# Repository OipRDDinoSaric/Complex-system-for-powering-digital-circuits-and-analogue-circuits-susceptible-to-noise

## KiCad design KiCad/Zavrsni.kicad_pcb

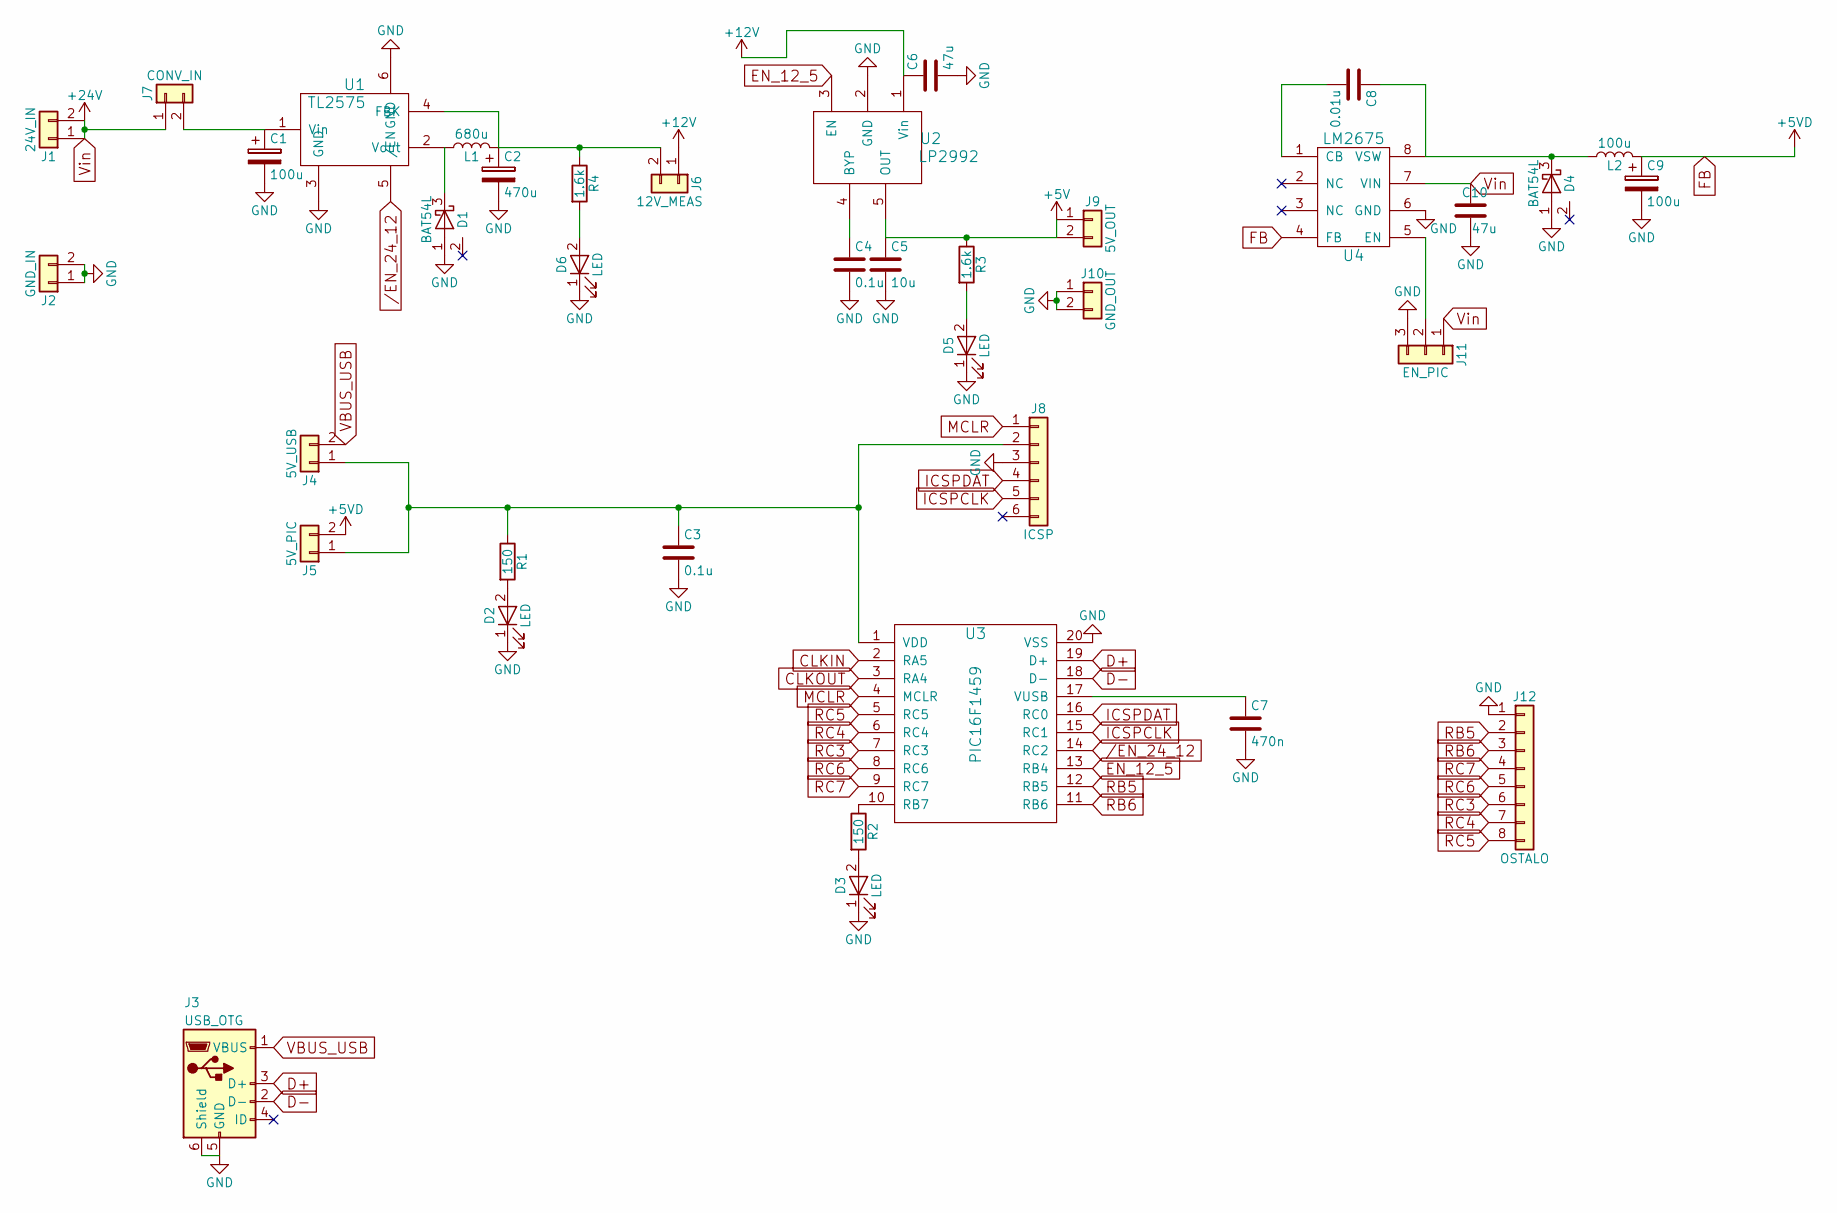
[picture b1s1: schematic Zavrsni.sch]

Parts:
C1: 100u; CP_Elec_6.3x7.7
C2: 470u; CP_Elec_10x10.5
C3: 0.1u; C_0402
C4: 0.1u; C_0805_HandSoldering
C5: 10u; C_1210_HandSoldering
C6, C10: 47u; C_1210_HandSoldering
C7: 470n; C_0805_HandSoldering
C8: 0.01u; C_0603_HandSoldering
C9: 100u; SM2917_POL
D1, D4: BAT54L; SOT-23_Handsoldering
D2, D3: LED; C_0603_HandSoldering
D5, D6: LED; Zelena dioda
J1: 24V_IN; Pin_Header_Straight_1x02_Pitch2.54mm
J2: GND_IN; Pin_Header_Straight_1x02_Pitch2.54mm
J3: USB_OTG; USB_Micro-B
J4: 5V_USB; Pin_Header_Straight_1x02_Pitch2.54mm
J5: 5V_PIC; Pin_Header_Straight_1x02_Pitch2.54mm
J6: 12V_MEAS; Pin_Header_Straight_1x02_Pitch2.54mm
J7: CONV_IN; Pin_Header_Straight_1x02_Pitch2.54mm
J8: ICSP; Pin_Header_Straight_1x06_Pitch2.54mm
J9: 5V_OUT; Pin_Header_Straight_1x02_Pitch2.54mm
J10: GND_OUT; Pin_Header_Straight_1x02_Pitch2.54mm
J11: EN_PIC; Pin_Header_Straight_1x03_Pitch2.54mm
J12: OSTALO; Pin_Header_Straight_1x08_Pitch2.54mm
L1: 680u; Coilcraft MSS1278T-684KLB 680uH
L2: 100u; Bourns_SRF0703A-101M_100u
R1, R2: 150; R_0805_HandSoldering
R3, R4: 1.6k; R_0402
U1: TL2575; TO-263-5
U2: LP2992; SOT-23-5_HandSoldering
U3: PIC16F1459; DIP-20_W7.62mm_LongPads
U4: LM2675; SOIC-8_3.9x4.9mm_Pitch1.27mm

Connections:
+5V: C5.1, J9.1, J9.2, R3.1, U2.5 (OUT)
+12V: C6.1, J6.1, U2.1 (Vin)
/EN_24_12: U1.5 (/EN), U3.14 (RC2)
CLKIN: U3.2 (RA5)
CLKOUT: U3.3 (RA4)
D+: J3.3 (D+), U3.19 (D+)
D-: J3.2 (D-), U3.18 (D-)
EN_12_5: U2.3 (EN), U3.13 (RB4)
FB: C9.1, J5.2, L2.2, U4.4 (FB)
GND: C1.2, C2.2, C3.2, C4.2, C5.2, C6.2, C7.2, C9.2, C10.1, D1.1 (A), D2.1 (K), D3.1 (K), D4.1 (A), D5.1 (K), D6.1 (K), J2.1, J2.2, J3.5 (GND), J3.6 (Shield), J8.3, J10.1, J10.2, J11.3, J12.1, U1.3 (GND), U1.6 (GND), U2.2 (GND), U3.20 (VSS), U4.6 (GND)
ICSPCLK: J8.5, U3.15 (RC1)
ICSPDAT: J8.4, U3.16 (RC0)
MCLR: J8.1, U3.4 (MCLR)
unnamed: C1.1, J7.2, U1.1 (Vin)
unnamed: C2.1, J6.2, L1.2, R4.1, U1.4 (FBK)
unnamed: C3.1, J4.1, J5.1, J8.2, R1.1, U3.1 (VDD)
unnamed: C4.1, U2.4 (BYP)
unnamed: C7.1, U3.17 (VUSB)
unnamed: C8.1, D4.3 (K), L2.1, U4.8 (VSW)
unnamed: C8.2, U4.1 (CB)
unnamed: D1.3 (K), L1.1, U1.2 (Vout)
unnamed: D2.2 (A), R1.2
unnamed: D3.2 (A), R2.2
unnamed: D5.2 (A), R3.2
unnamed: D6.2 (A), R4.2
unnamed: J11.2, U4.5 (EN)
unnamed: R2.1, U3.10 (RB7)
RB5: J12.2, U3.12 (RB5)
RB6: J12.3, U3.11 (RB6)
RC3: J12.6, U3.7 (RC3)
RC4: J12.7, U3.6 (RC4)
RC5: J12.8, U3.5 (RC5)
RC6: J12.5, U3.8 (RC6)
RC7: J12.4, U3.9 (RC7)
VBUS_USB: J3.1 (VBUS), J4.2
Vin: C10.2, J1.1, J1.2, J7.1, J11.1, U4.7 (VIN)

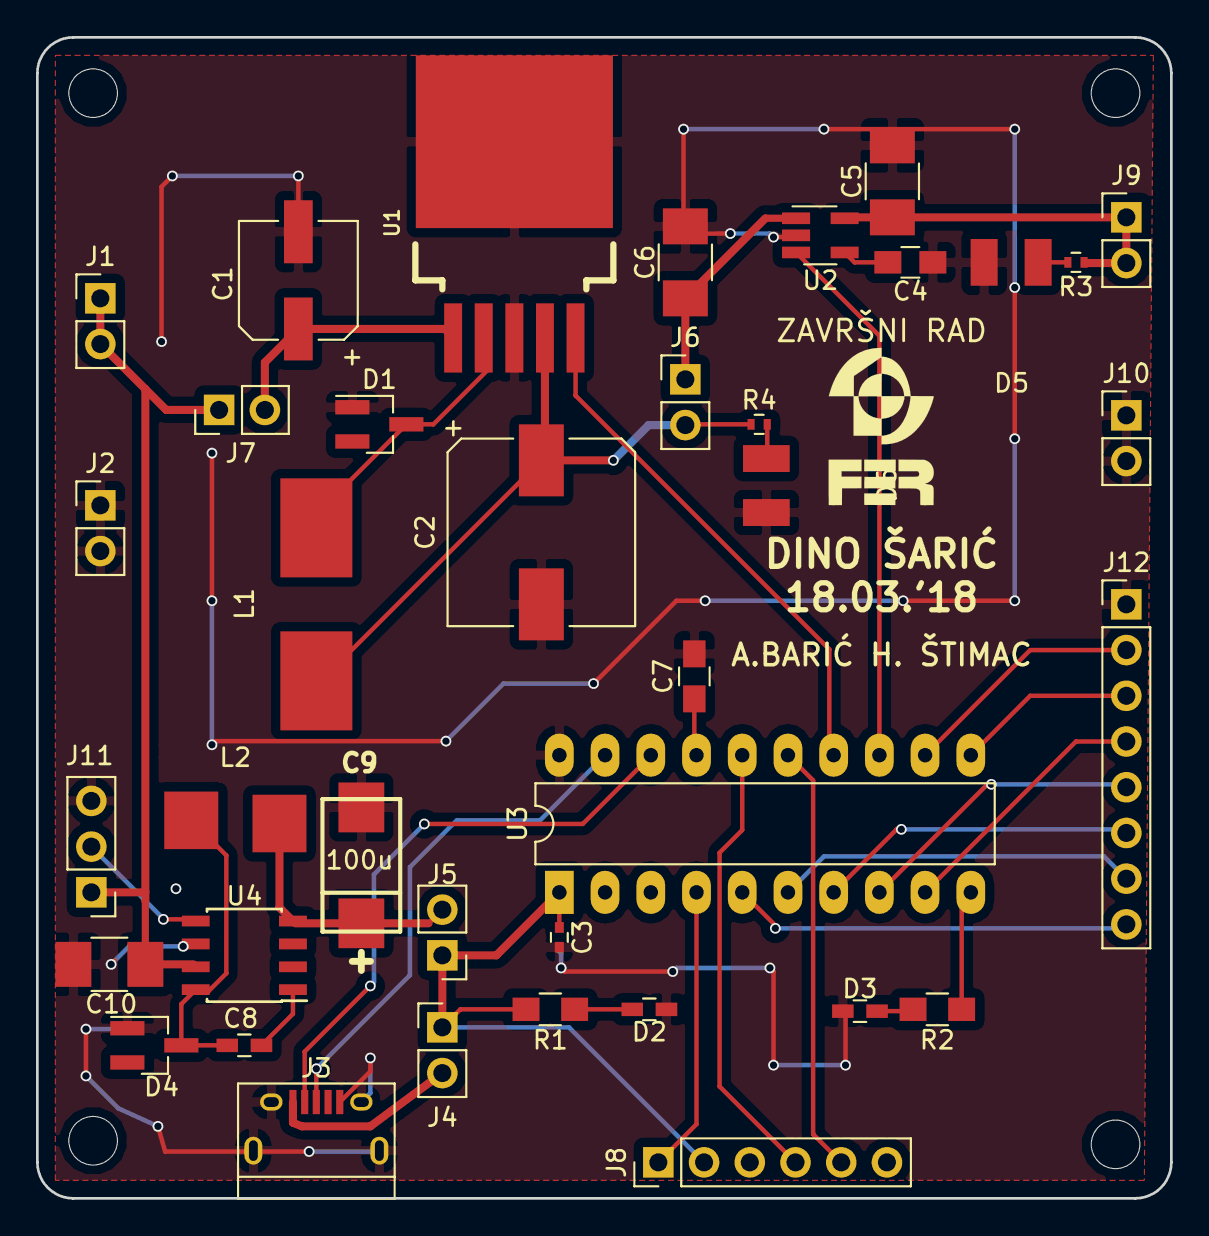
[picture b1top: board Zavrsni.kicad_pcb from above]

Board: 2 copper layers, 63.0 x 64.5 mm, 39 parts (0 on the bottom side), 34 nets.

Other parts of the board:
VAL: FERlogov3NEGBMP_025in

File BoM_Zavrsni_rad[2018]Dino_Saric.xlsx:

Value | Designator | Description | Case Style | Manufacturer | Order Code | Quantity | Price, GBP | Total price |  | Link:
 | U4 | LM2675M-5.0 - Buck (Step Down) Switching Regulator, Fixed, 6.5V-40V In, 5V And 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 | SOIC-8 | TEXAS INSTRUMENTS | 9489746 | 2 | 4,21 | 8.42 |  | http://export.farnell.com/texas-instruments/lm2675m-5-0/swit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
100u | L2 | SRF0703A-101M - Inductor, Coupled, 100 µH, 20%, 0.715 ohm, 730 mA, 7.6mm x 7.6m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 | Datasheet | BOURNS | 2455003 | 2 | 0,863 | 1.726 |  | http://export.farnell.com/bourns/srf0703a-101m/inductor-coup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
47u | C10 | C1210C476M9PACTU - SMD Multilayer Ceramic Capacitor, 1210 [3225 Metric], 47 µF,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 | 1210 | KEMET | 1108327 | 2 | 0,897 | 1.794 |  | http://export.farnell.com/kemet/c1210c476m9pactu/cap-mlcc-x5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
- | D4 | NSVBAT54LT1G - Small Signal Schottky Diode, Single, 30 V, 200 mA, 800 mV, 600 m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 | SOT-23 | ON SEMICONDUCTOR | 2774594 | 5 | 0,0366 | 0.183 |  | http://export.farnell.com/on-semiconductor/nsvbat54lt1g/diod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
100u | C9 | TPSD107K010R0100... - Surface Mount Tantalum Capacitor, 100 µF, 10 V, TPS Serie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 | 2917 | AVX | 1462462 | 2 | 0,922 | 1.8440000000000001 |  | http://export.farnell.com/avx/tpsd107k010r0100/cap-tant-100u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
0,01u | C8 | 0603B103K250CT - SMD Multilayer Ceramic Capacitor, 0603 [1608 Metric], 0.01 µF,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 | 0603 | WALSIN | 2496827 | 10 | 0,0129 | 0.129 |  | http://export.farnell.com/walsin/0603b103k250ct/capacitor-ml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
 |  |  |  |  |  |  |  | 0
 | U1 | TL2575-12IKTTR - Buck (Step Down) Switching Regulator, Fixed, 4.75V-40V In, 12V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 | T0-263-5 | TEXAS INSTRUMENTS | 1755279 | 2 | 1,69 | 3.38 |  | http://export.farnell.com/texas-instruments/tl2575-12ikttr/i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
100u | C1 | EEEFPV101XAP - SMD Aluminium Electrolytic Capacitor, Radial Can - SMD, 100 µF, 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 | Datasheet | PANASONIC ELECTRONIC COMPONENTS | 1539501 | 2 | 0,395 | 0.79 |  | http://export.farnell.com/panasonic-electronic-components/ee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
470u | C2 | EEEFK1V471SP - SMD Aluminium Electrolytic Capacitor, Radial Can - SMD, 470 µF, 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 | Datasheet | PANASONIC ELECTRONIC COMPONENTS | 2507737 | 2 | 0,959 | 1.9179999999999999 |  | http://export.farnell.com/panasonic-electronic-components/ee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
- | D1 | Kao D4 u retku 6 | SOT-23 | ON SEMICONDUCTOR | 2774594 | 0 | 0,0366 | 0 |  | http://export.farnell.com/on-semiconductor/nsvbat54lt1g/diod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
680u | L1 | MSS1278T-684KLB - Power Inductor (SMD), 680 µH, 750 µA, Shielded, 1.24 A, MSS12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 | Datasheet | COILCRAFT | 2288523 | 2 | 0,804 | 1.6080000000000001 |  | http://export.farnell.com/coilcraft/mss1278t-684klb/inductor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
 |  |  |  |  |  |  |  | 0
- | U2 | LP2992AIM5-5.0/NOPB - Fixed LDO Voltage Regulator, 2.2V to 16V, 450mV Dropout, 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 | SOT-23 | TEXAS INSTRUMENTS | 1685561 | 2 | 0,818 | 1.6359999999999999 |  | http://export.farnell.com/texas-instruments/lp2992aim5-5-0-n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
0,1u | C4 | VJ0805Y104JCAAJ - SMD Multilayer Ceramic Capacitor, IR Reflow, 0805 [2012 Metri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 | 0805 | VISHAY | 2672814 | 2 | 0,361 | 0.72199999999999998 |  | http://export.farnell.com/vishay/vj0805y104jcaaj/cap-mlcc-x7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
47u | C6 | C1210C476M9PACTU - SMD Multilayer Ceramic Capacitor, 1210 [3225 Metric], 47 µF,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 | 1210 | KEMET | 1108327 | 2 | 0,897 | 1.794 |  | http://export.farnell.com/kemet/c1210c476m9pactu/cap-mlcc-x5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
10u | C5 | 1210X106K250CT - SMD Multilayer Ceramic Capacitor, 1210 [3225 Metric], 10 µF, 2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 | 1210 | WALSIN | 2497182 | 2 | 0,419 | 0.83799999999999997 |  | http://export.farnell.com/walsin/1210x106k250ct/capacitor-ml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
 |  |  |  |  |  |  |  | 0
- | U3 | PIC16F1459-I/P - 8 Bit Microcontroller, Flash, PIC16F145x, 48 MHz, 14 KB, 1 KB,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 | DIP-20 | MICROCHIP | 2305816 | 2 | 1,81 | 3.62 |  | http://export.farnell.com/microchip/pic16f1459-i-p/mcu-8bit-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
0,1u | C3 | VJ0805Y104JCAAJ - SMD Multilayer Ceramic Capacitor, IR Reflow, 0805 [2012 Metri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 | 0805 | VISHAY | 2672814 | 2 | 0,361 | 0.72199999999999998 |  | http://export.farnell.com/vishay/vj0805y104jcaaj/cap-mlcc-x7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
470n | C7 | 885012007025 - SMD Multilayer Ceramic Capacitor, 0805 [2012 Metric], 4700 pF, 1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 | 0805 | WURTH ELEKTRONIK | 2812146 | 5 | 0,124 | 0.62 |  | http://export.farnell.com/wurth-elektronik/885012007025/cap-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
- | J1, J2, J4, J5, J6, J7, J9, J10 | 2211S-02G - Board-To-Board Connector, Vertical, 2.54 mm, 2 Contacts, Header, 22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 | Through hole, 01x02, 2,54 mm | MULTICOMP | 1593411 | 16 | 0,0204 | 0.32640000000000002 |  | http://export.farnell.com/multicomp/2211s-02g/header-1-row-v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
- | J8 | TSM-106-01-L-SH - Board-To-Board Connector, 2.54 mm, 6 Contacts, Header, TSM Se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 | Through hole, 01x06, 2,54 mm | SAMTEC | 2667444 | 2 | 0,671 | 1.3420000000000001 |  | http://export.farnell.com/samtec/tsm-106-01-l-sh/connector-h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
- | J12 | 90120-0768 - Board-To-Board Connector, Vertical, 2.54 mm, 8 Contacts, Header, C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 | Through hole, 01x08, 2,54 mm | MOLEX | 9733345 | 2 | 0,45 | 0.9 |  | http://export.farnell.com/molex/90120-0768/header-vertical-1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
- | J11 | 2211S-03G - Board-To-Board Connector, Vertical, 2.54 mm, 3 Contacts, Header, 22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 | Through hole, 01x03, 2,54 mm | MULTICOMP | 1593412 | 2 | 0,0269 | 5.3800000000000001E-2 |  | http://export.farnell.com/multicomp/2211s-03g/header-1-row-v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
- | J3 | ZX62-B-5PA(33) - USB Connector, Micro USB Type B, USB 2.0, Receptacle, 5 Ways, 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 | Surface Mount, Right Angle | HIROSE(HRS) | 2554978 | 2 | 0,38 | 0.76 |  | http://export.farnell.com/hirose-hrs/zx62-b-5pa-33/micro-usb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
- | D2, D3 | KPT-1608EC - LED, Low Power, Red, SMD, 0.8mm x 1.6mm, 20 mA, 2 V, 617 nm | 0603 | KINGBRIGHT | 2099221 | 5 | 0,0375 | 0.1875 |  | http://export.farnell.com/kingbright/kpt-1608ec/led-0603-red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
150 | R1, R2 | MCWR08X1500FTL - SMD Chip Resistor, 150 ohm, MCWR Series, 150 V, Thick Film, 08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 | 0805 | MULTICOMP | 2447574 | 10 | 0,006 | 0.06 |  | http://export.farnell.com/multicomp/mcwr08x1500ftl/res-thick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
- | U3 | 2227MC-20-03-07-F1 - IC & Component Socket, 20 Contacts, DIP Socket, 2.54 mm, 2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 | DIP-20 | MULTICOMP | 1103848 | 2 | 0,457 | 0.91400000000000003 |  | http://export.farnell.com/multicomp/2227mc-20-03-07-f1/socke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
 |  |  |  |  |  |  |  | 0
1,6k | R3 | MCMR04X162 JTL - SMD Chip Resistor, Ceramic, 1.6 kohm, MCMR Series, 50 V, Thick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 | 0402 | MULTICOMP | 2072674 | 10 | 0,0017 | 1.6999999999999998E-2 |  | http://export.farnell.com/multicomp/mcmr04x162-jtl/res-ceram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
- | D5, D6 | LGT67K-H2K1-24-Z - LED, Hyper TOPLED®, Green, SMD, 2.4mm, 2 mA, 1.8 V, 570 nm | Datasheet | OSRAM | 1226376 | 5 | 0,174 | 0.86999999999999988 |  | http://export.farnell.com/osram/lgt67k-h2k1-24-z/led-smd-gre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
5,1k | R4 | MCWR08X5101FTL - SMD Chip Resistor, 5.1 kohm, MCWR Series, 150 V, Thick Film, 0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 | 0805 | MULTICOMP | 2447692 | 10 | 0,006 | 0.06 |  | http://export.farnell.com/multicomp/mcwr08x5101ftl/res-thick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
 |  |  |  |  |  |  |  | 0
 |  |  |  |  |  |  |  | 0
 |  |  |  |  |  |  |  | 0
 |  |  |  |  |  |  | SUMA, GPB | 37.234700000000011

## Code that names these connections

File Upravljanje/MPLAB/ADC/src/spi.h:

void SPI_Init(){
    TRISB6 = 0;     // set RB6 == SPI_CLK as output
    TRISB4 = 1;     // set RB4 == SPI_SDI as input
    TRISC7 = 0;     // set RC7 == SPI_SDO as output
    TRISB5 = 0;     // set RC6 == SPI_SS as output

    PIR1bits.SSP1IF = 0;        // Clear interrupt flag
    PIE1bits.SSP1IE = 0;        // Disable MSSP interrupt
    //INTCONbits.PEIE = 0;        // Disable periferal interrupts

    SSPCON1bits.SSPEN = 1;      // enable serial port
    SSPCON1bits.CKP = 1;        // clock IDLE state is HIGH
    SSPSTATbits.CKE = 1;        // Data transmitted from ACTIVE to IDLE clock
    SSPCON1bits.SSPM = 0x01;    // Master mode, clock = FOSC/64
    SSPSTATbits.SMP = 0;        // input sampled at middle of interval
}

void SPI_Write(char data){
    unsigned char TempVar;
    TempVar = SSP1BUF;              // Clear buffer by reading
    PIR1bits.SSP1IF = 0;            // Clear interrupt flag
    SSP1BUF = data;                 // write byte to SSP1BUF register
    while(!PIR1bits.SSP1IF);        // wait until bus cycle complete
}


unsigned char SPI_Read(void){
   SSPBUF = 0x00;                  // initiate bus cycle
   while ( !SSPSTATbits.BF );      // wait until cycle complete
   return ( SSPBUF );              // return with byte read 
}
 
